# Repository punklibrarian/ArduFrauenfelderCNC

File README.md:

ArduFrauenfelderCNC
=============================
Copyright 2011 Design Tech Industries (DTI)  & Tamworth Hackerspace

DTI email: <the.righteous.avengers@gmail.com> |
THS: <http://tamworthhackerspace.org> |
Google Group: <https://groups.google.com/group/tamworth-hackerspace>

The ArduFrauenfelderCNC is a CNC mill run by an Arduino compatible custom board with 
stepper motor drivers, running grbl.

Board Features:

 * ATmega328 & ATmega32U4 MCU
 * Power LED & Reset switch
 * Populated pins for FTDI breakout board
 * SparkFun EasyDriver v4.4
 * Open Source; OSHW compliant
 * Design files freely available

Mill features:

 * Designed using free tools
 * Simple construction methods
 * Design files freely available

In this repository you will find the gerber files, project (.pro), board (.brd) and schematic (.sch), 
along with a grbl file configured specifically for the board.

**At the moment the files you find here are in the process of development and as such are not 
production ready. It is an ongoing endeavour to create the board and mill satisfactorily. If you can 
help in this regard please contact me, as well as if you find something that needs correction**

**The only files that can be manufactured are those of the ArduFrauenfelderCNC 1.0 - Arduino Pro Micro Edition. 
It should be a fully functional design. As on 20/07/2012 still untested.**

INSIDE THIS REPOSITORY
----------------------
The 'docs' folder within this repository includes a handy copy of the schematic in PNG format and images 
of the pcb/mill, along with assembly documentation.

The 'mill' folder within this repository has design files for the physical mill and documentation 
for it's construction. It has 'sketchup_exported_faces', 'sketchup_models' and 'laser_cutting' folders.
**For license information refer to the attached README.md file in the 'mill' folder**

The 'controller' folder within this repository has all the files needed to create the controller board. 
It has folders for the specific MCU used, 'ATmega328', 'ATmega32U4' (inside these folders are 'EAGLE', 'eagleUp', 
'KiCad' and 'gerbers' folders).

**For license information refer to the attached README.md file in the 'controller' folder**

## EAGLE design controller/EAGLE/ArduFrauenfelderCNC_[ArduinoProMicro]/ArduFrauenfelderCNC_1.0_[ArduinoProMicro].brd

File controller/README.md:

ArduFrauenfelderCNC >> Controller Board
=======================================
Copyright 2012 Design Tech Industries (DTI)  & Tamworth Hackerspace

In the 'controller' folder of this repository you can find the design files for the CNC controller board in an ATmega328 
and ATmega32U4 variety. You will find project files in EAGLE and KiCad formats, as well as completed gerber files for the 
board ready to be sent to BatchPCB and OSH Park, which are the the services I designed this board to use, for manufacture.

I have also added eagleUp (http://eagleup.wordpress.com) files as well as a SKP of the resulting conversion 
(minus parts as there aren't any at the moment).

You will also find a customised version of Grbl in the form of a .HEX file. Later versions of the controller 
board will use rStep and be based on the ATmega644p MCU (I am also looking at using an mbed and http://smoothieware.org).

INSTALLATION
------------
**EAGLE**
The design is saved as an EAGLE project. EAGLE PCB design software is available from www.cadsoftusa.com 
free for non-commercial use and can be installed on Windows and Mac, with Linux support through WINE. 
To use this project download it and place the directory containing these files into the "eagle" directory 
on your computer. Then open EAGLE and navigate to Projects -> eagle -> ArduFrauenfelderCNC.

**KiCad**
KiCad EDA Suite is an Open Source alternative to EAGLE. It is available on Windows and Linux and can be installed 
on Mac. It is available from http://kicad.sourceforge.net and works in a similar way to EAGLE. You will find project 
files for KiCad in the aptly named folder in this repository. To use this project download it and place the directory 
containing these files into a folder of your choice. Then open KiCad and navigate to File -> Open -> 
'FOLDER_OF_YOUR_CHOICE' -> ArduFrauenfelderCNC.pro

You will also find a manual in the 'docs' folder for the assembly of the controller board, with colour photos and diagrams. 
**Documentation is separately licensed. See LICENSE section below**

DISTRIBUTION
------------
The specific terms of distribution of this project are governed by the license referenced below.

LICENSE
-------
> CONTROLLER BOARD
> ----------------
> This work is licensed under the Creative Commons Attribution-ShareAlike License.  
> 
> To view a copy of this license, visit:
> 
>   http://creativecommons.org/licenses/by-sa/3.0/  
>   http://creativecommons.org/licenses/by-sa/3.0/legalcode
> 
> or send a letter to
> 
>   Creative Commons  
>   171 Second Street, Suite 300  
>   San Francisco  
>   California, 94105  
>   USA

> DOCUMENTATION
> -------------
> This work is licensed under the GNU Free Documentation License Version 1.3
> 
> To view a copy of this license, visit:
> 
>   http://www.gnu.org/licenses/fdl-1.3.html

The "license" folder within this repository also contains copies of the
license(s) referenced above.

CREDITS
-------
The ArduFrauenfelderCNC was designed by Jamie Johnston (jameskun89@rocketmail.com) 
based on previous work by the Arduino team (www.arduino.cc/playground/Main/People) 
which includes:

 * Massimo Banzi
 * David Cuartielles
 * Tom Igoe
 * Gianluca Martino
 * David A. Mellis

As well as Brian Schmalz, the creator of the EasyDriver Stepper Motor Driver (http://schmalzhaus.com/EasyDriver) 
and Sparkfun, the creator of the Arduino Pro Micro (http://www.sparkfun.com/products/11098).

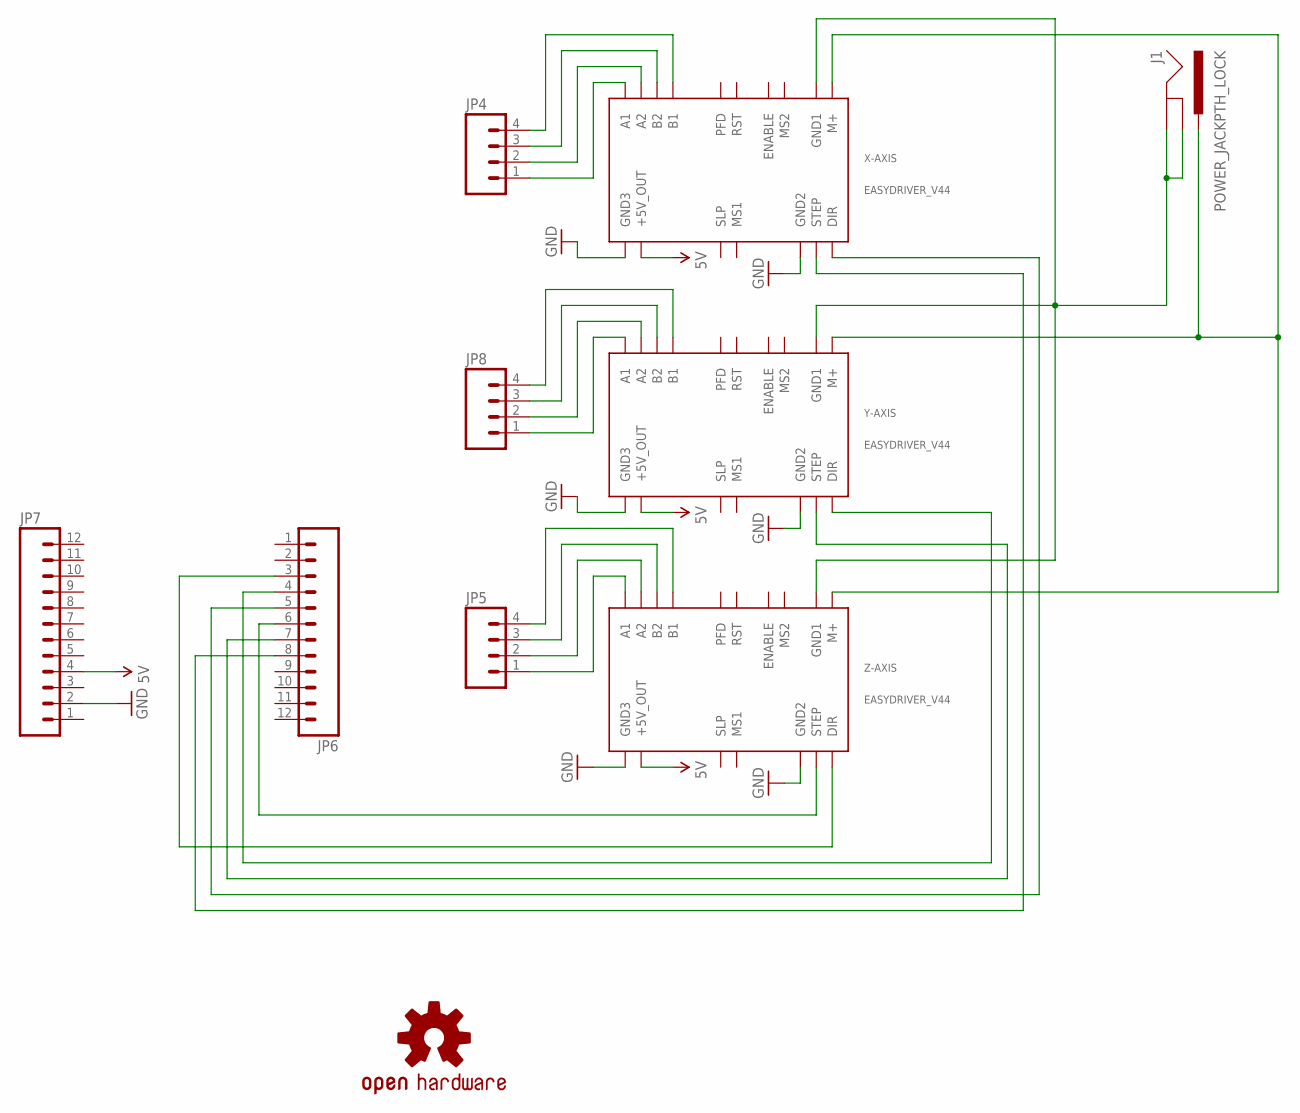
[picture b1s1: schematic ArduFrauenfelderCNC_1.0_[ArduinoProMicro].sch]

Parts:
J1: POWER_JACKPTH_LOCK; POWER_JACK_PTH_LOCK
JP4, JP5, JP8: M04LOCK_LONGPADS; 1X04_LOCK_LONGPADS
JP6, JP7: M12PTH; 1X12
U$2: OSHW-LOGOM; OSHW-LOGO-M
X-AXIS: EASYDRIVER_V44
Y-AXIS: EASYDRIVER_V44
Z-AXIS: EASYDRIVER_V44

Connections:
5V: JP7.4, X-AXIS.P$11 (+5V_OUT), Y-AXIS.P$11 (+5V_OUT), Z-AXIS.P$11 (+5V_OUT)
GND: JP7.2, X-AXIS.GND2, X-AXIS.GND3, Y-AXIS.GND2, Y-AXIS.GND3, Z-AXIS.GND2, Z-AXIS.GND3
unnamed: J1.GND, J1.GNDBREAK, X-AXIS.GND1, Y-AXIS.GND1, Z-AXIS.GND1
unnamed: JP4.1, X-AXIS.A1
unnamed: JP4.2, X-AXIS.A2
unnamed: J1.PWR, X-AXIS.M+, Y-AXIS.M+, Z-AXIS.M+
unnamed: JP4.3, X-AXIS.B2
unnamed: JP4.4, X-AXIS.B1
unnamed: JP8.1, Y-AXIS.A1
unnamed: JP8.2, Y-AXIS.A2
unnamed: JP8.3, Y-AXIS.B2
unnamed: JP8.4, Y-AXIS.B1
unnamed: JP5.1, Z-AXIS.A1
unnamed: JP5.2, Z-AXIS.A2
unnamed: JP5.3, Z-AXIS.B2
unnamed: JP5.4, Z-AXIS.B1
unnamed: JP6.8, X-AXIS.STEP
unnamed: JP6.5, X-AXIS.DIR
unnamed: JP6.7, Y-AXIS.STEP
unnamed: JP6.4, Y-AXIS.DIR
unnamed: JP6.6, Z-AXIS.STEP
unnamed: JP6.3, Z-AXIS.DIR

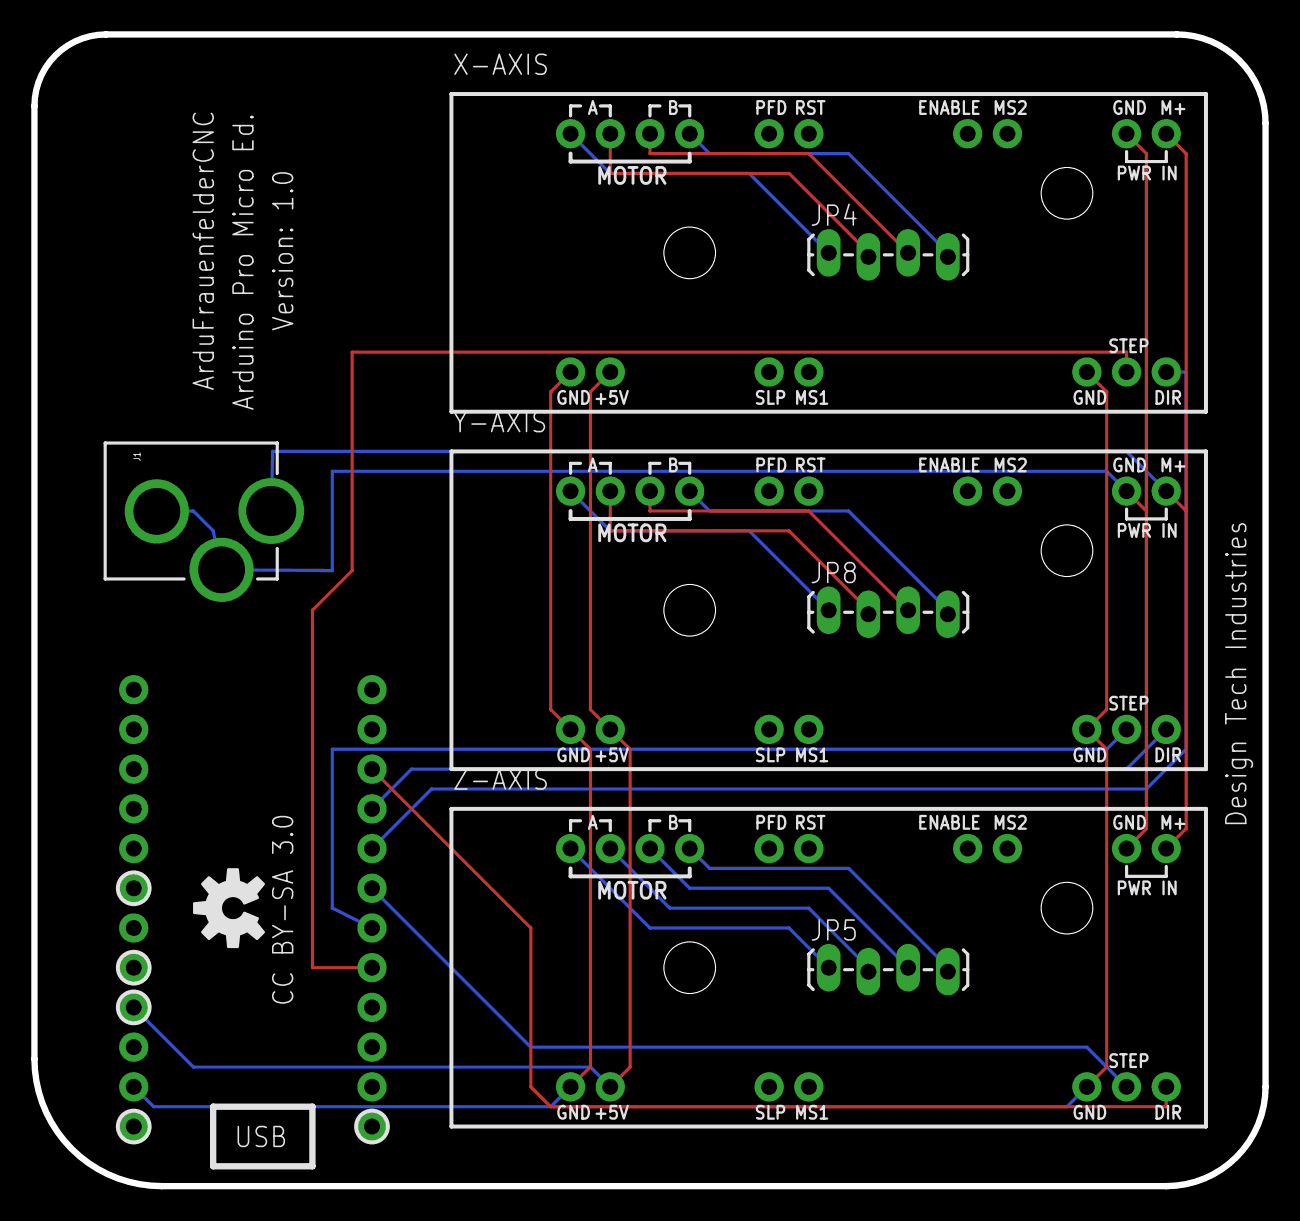
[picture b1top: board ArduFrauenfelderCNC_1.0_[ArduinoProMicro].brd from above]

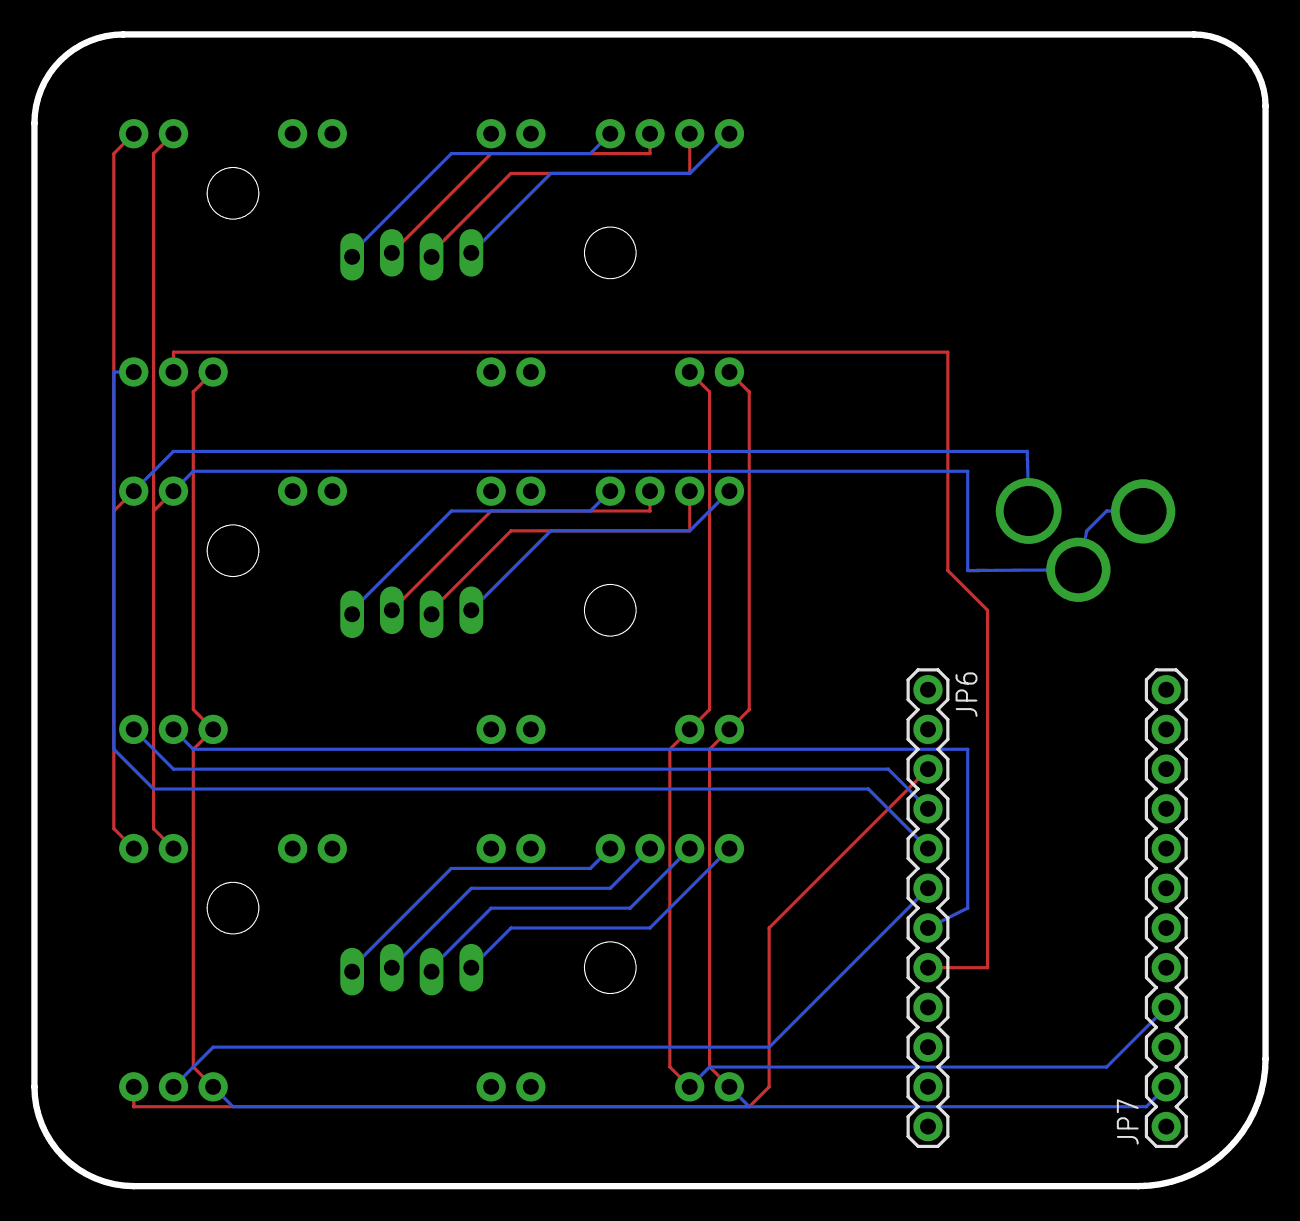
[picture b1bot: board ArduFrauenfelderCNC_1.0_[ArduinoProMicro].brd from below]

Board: 2 copper layers, 78.7 x 73.7 mm, 10 parts (2 on the bottom side), 22 nets.

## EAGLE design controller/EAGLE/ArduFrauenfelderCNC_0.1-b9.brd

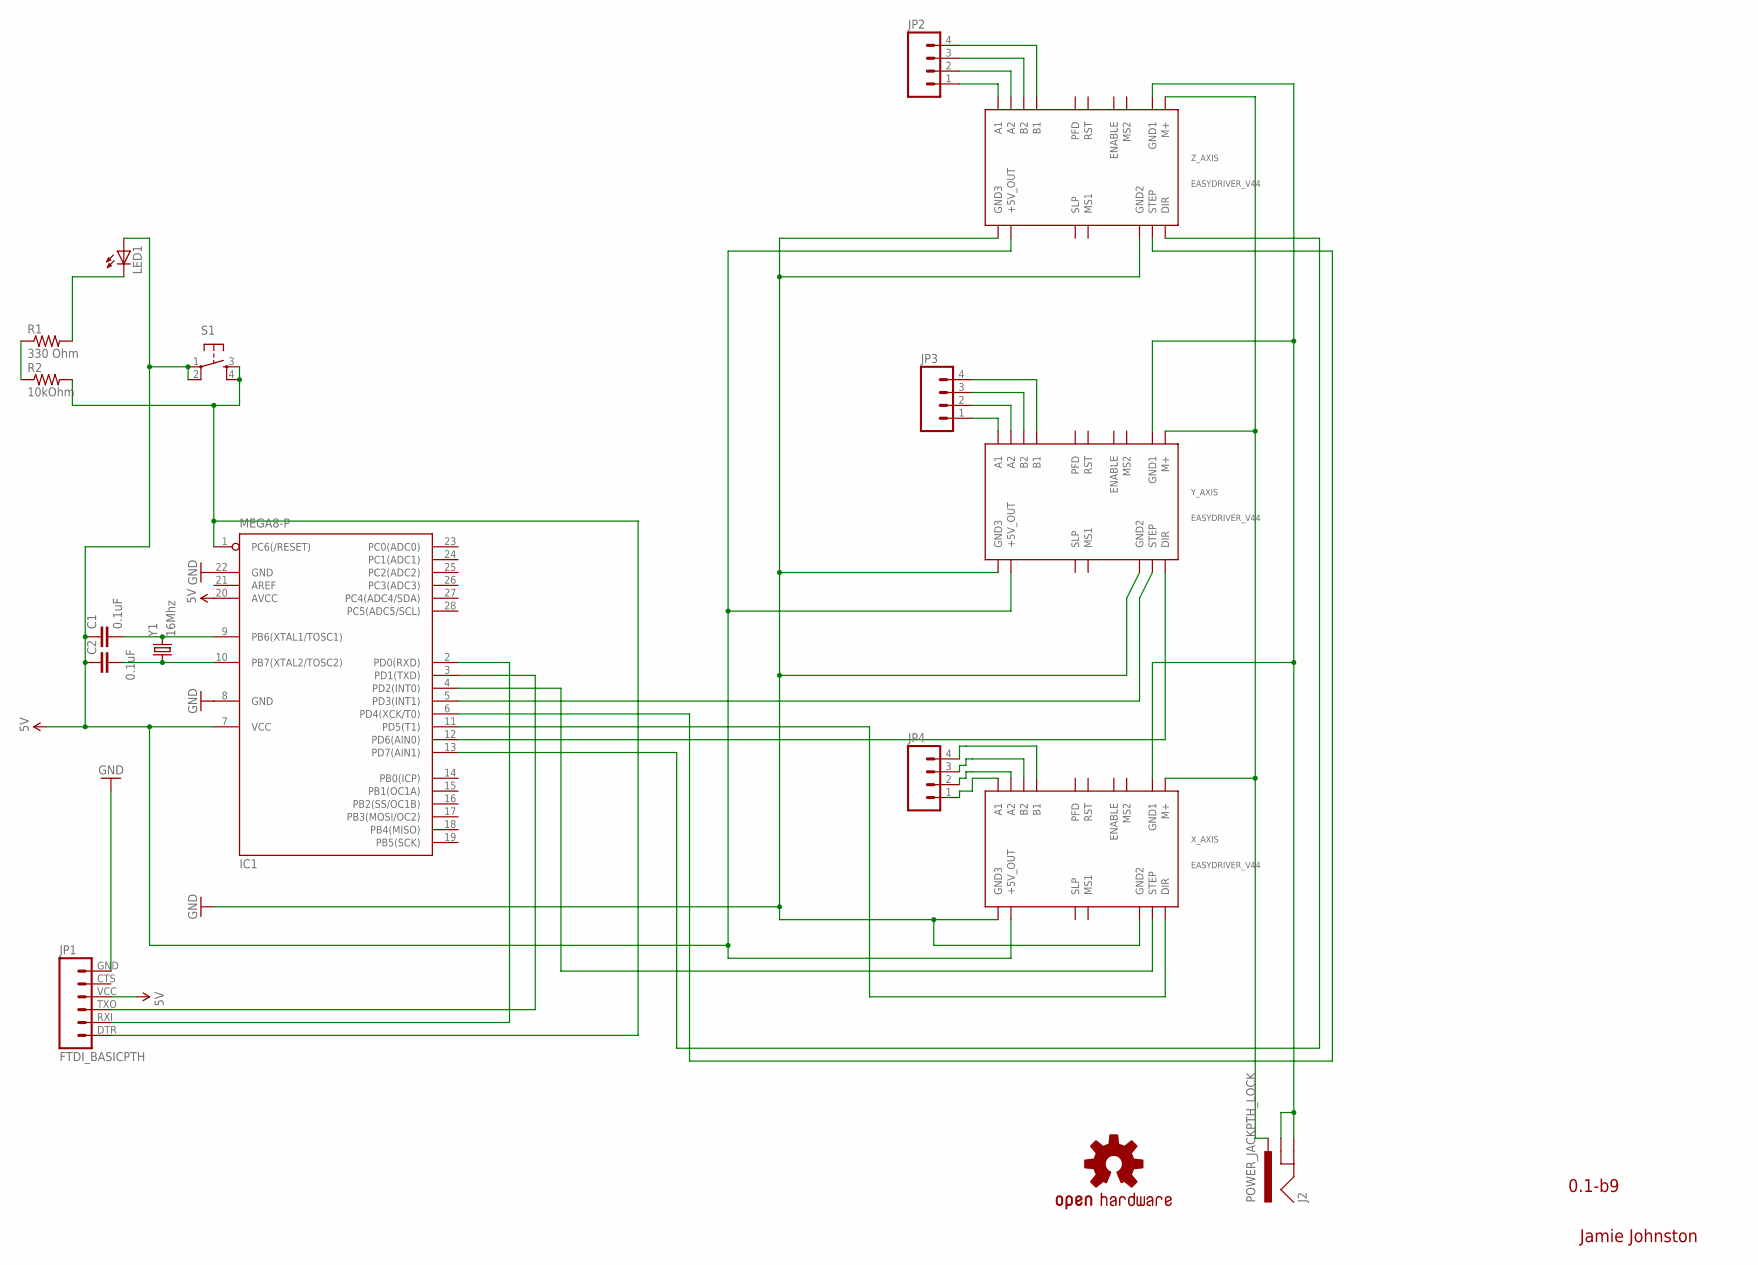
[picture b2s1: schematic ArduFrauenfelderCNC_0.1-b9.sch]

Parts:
C1, C2: 0.1uF; CAP-PTH-SMALL
IC1: MEGA8-P; DIL28-3
J2: POWER_JACKPTH_LOCK; POWER_JACK_PTH_LOCK
JP1: FTDI_BASICPTH; FTDI_BASIC
JP2, JP3, JP4: M04LOCK; 1X04_LOCK
LED1: LED5MM
R1: 330 Ohm; AXIAL-0.4
R2: 10kOhm; AXIAL-0.4
S1: TAC_SWITCHPTH; TACTILE-PTH
U$2: OSHW-LOGOL; OSHW-LOGO-L
X_AXIS: EASYDRIVER_V44
Y1: 16Mhz; HC49US
Y_AXIS: EASYDRIVER_V44
Z_AXIS: EASYDRIVER_V44

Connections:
5V: C1.1, C2.1, IC1.7 (VCC), IC1.20 (AVCC), JP1.VCC (4), LED1.A, S1.1, S1.2, X_AXIS.P$11 (+5V_OUT), Y_AXIS.P$11 (+5V_OUT), Z_AXIS.P$11 (+5V_OUT)
GND: IC1.8 (GND), IC1.22 (GND), JP1.GND (6), X_AXIS.GND2, X_AXIS.GND3, Y_AXIS.GND2, Y_AXIS.GND3, Z_AXIS.GND2, Z_AXIS.GND3
unnamed: C1.2, IC1.9 (PB6(XTAL1/TOSC1)), Y1.2
unnamed: C2.2, IC1.10 (PB7(XTAL2/TOSC2)), Y1.1
unnamed: IC1.5 (PD3(INT1)), Y_AXIS.STEP
unnamed: LED1.K (C), R1.P$2 (2)
unnamed: IC1.1 (PC6(/RESET)), JP1.DTR (1), R2.P$2 (2), S1.3, S1.4
unnamed: R1.P$1 (1), R2.P$1 (1)
unnamed: JP2.1, Z_AXIS.A1
unnamed: J2.PWR, X_AXIS.M+, Y_AXIS.M+, Z_AXIS.M+
unnamed: JP2.2, Z_AXIS.A2
unnamed: J2.GND, J2.GNDBREAK, X_AXIS.GND1, Y_AXIS.GND1, Z_AXIS.GND1
unnamed: IC1.3 (PD1(TXD)), JP1.TXO (3)
unnamed: IC1.2 (PD0(RXD)), JP1.RXI (2)
unnamed: IC1.12 (PD6(AIN0)), Y_AXIS.DIR
unnamed: IC1.4 (PD2(INT0)), X_AXIS.STEP
unnamed: JP2.3, Z_AXIS.B2
unnamed: IC1.11 (PD5(T1)), X_AXIS.DIR
unnamed: JP2.4, Z_AXIS.B1
unnamed: JP3.1, Y_AXIS.A1
unnamed: IC1.13 (PD7(AIN1)), Z_AXIS.DIR
unnamed: IC1.6 (PD4(XCK/T0)), Z_AXIS.STEP
unnamed: JP3.2, Y_AXIS.A2
unnamed: JP3.3, Y_AXIS.B2
unnamed: JP3.4, Y_AXIS.B1
unnamed: JP4.1, X_AXIS.A1
unnamed: JP4.2, X_AXIS.A2
unnamed: JP4.3, X_AXIS.B2
unnamed: JP4.4, X_AXIS.B1

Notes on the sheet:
Jamie Johnston
0.1-b9

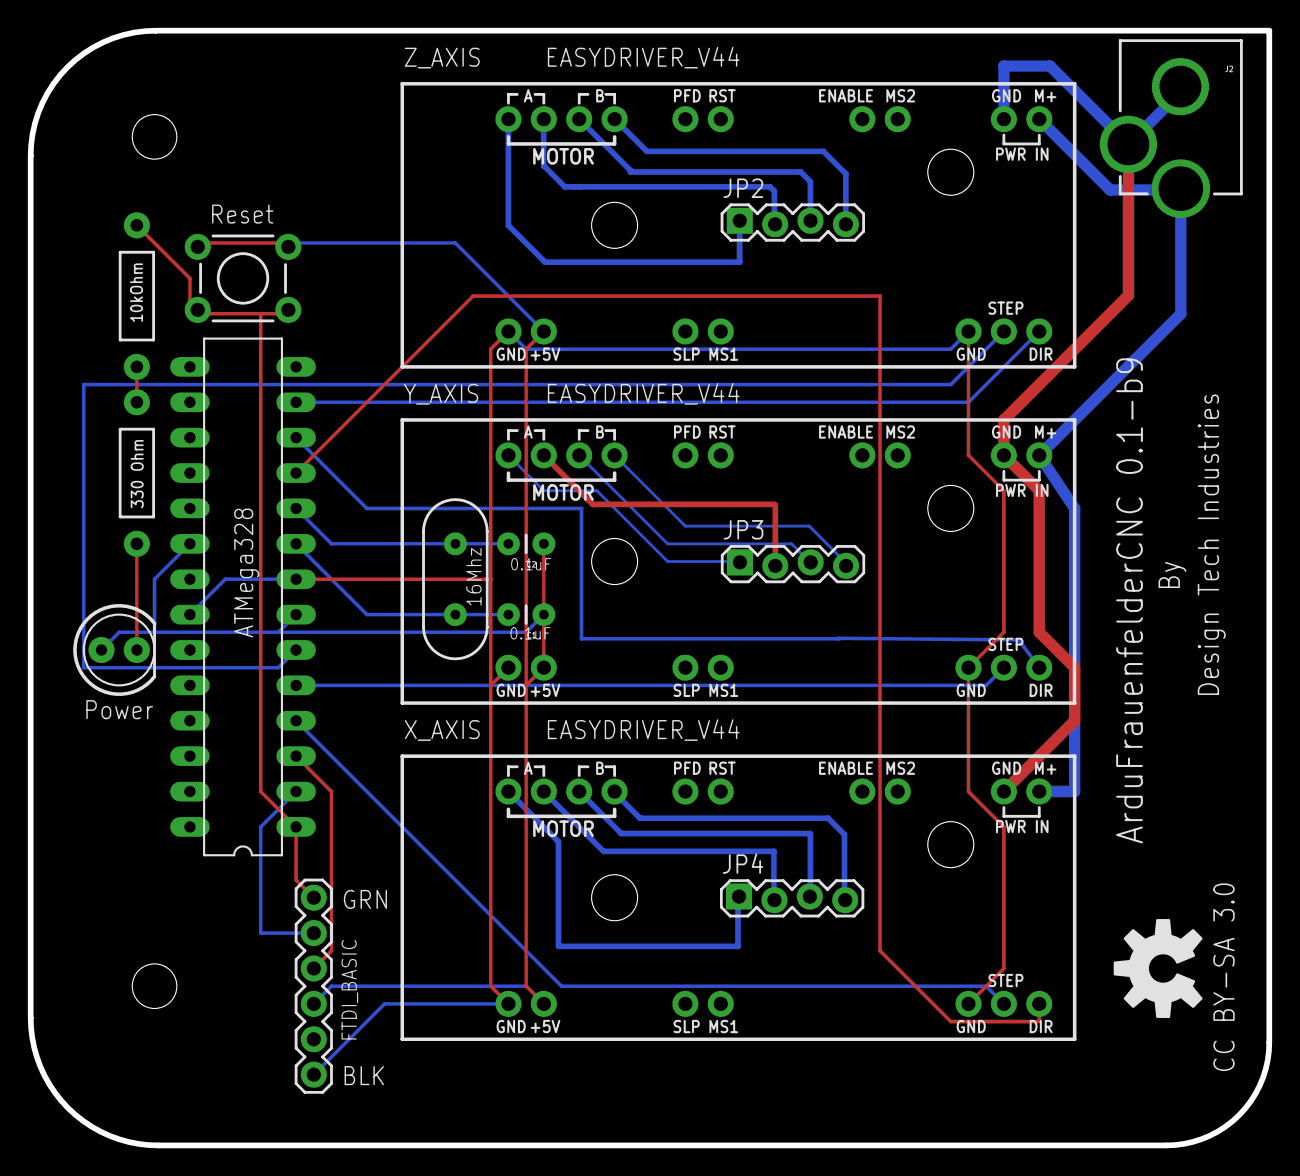
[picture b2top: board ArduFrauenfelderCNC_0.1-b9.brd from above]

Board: 2 copper layers, 88.9 x 80.0 mm, 17 parts (0 on the bottom side), 29 nets.

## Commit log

2011-11-18 Initial Commit -Jamie
2011-11-18 Edit to README.md formatting.
2011-11-18 Re-edit of README.md formatting.
2011-11-18 Changed file/folder structure so as to aid in program identification.
2011-11-19 Added Open Hardware symbol, board name, board version, board license (CC BY-SA 3.0), drill hole markers and reference to designing parties (DTI and THS).
2011-11-19 Found GND pins connected to +5v power pins. Rectified and traces are now more organised (only one jumper wire needed). Updated version to 0.1-b3.
2011-11-19 Conversion of EAGLE schematic to KiCad format (untested), using eagle2kicad.ulp V1.1
2011-11-19 Minor content change to README.md: added stop-gap material about included KiCad design files (more to be written later) and acknowledging Brian Schmalz in credits.
2011-11-19 New image of altered schematic (0.1-b2 => 0.1-b3), plus added version detail, OSHW logo and increase in image quality.
2011-11-19 Added version detail to schematic, as well as creators name and OSHW logo.
2011-11-19 Slight edit: added extra OSHW logo to board due to addition of logo to schematic.
2011-11-19 Update of schematic for KiCad (untested). Converted using eagle2kicad.ulp V1.1 and includes an initial commit of the .lib and .pro files.
2011-11-19 Minor edit: repositioned second OSHW logo, added GRN & BLK to tPlace layer and changed tDocu layer colour to yellow.
2011-11-20 Creation and initial commit of prototype Gerber files using SparkFun's CAM file (sfe-gerb274x.cam). Included are the seven files needed by fab houses and a tar.gz copy of files for ease of use.
2011-11-20 Altered README.md wording and added mention of Gerber files.
2011-11-20 Change to folder name.
2011-11-20 Changed README.md structure, adding what can found inside the repository and changed the description of project.
2011-11-20 Added license, GNU Free Documentation License Version Version 1.3, for future documentation. Also changed name of Creative Commons license to include version.
2011-11-20 Initial commit of 'mill' folder and its README.md file.
2011-11-20 Temporary delete.
2011-11-20 Re-commit of previously named 'Gerber' folder. Change of name to 'gerber'.
2011-11-20 Edit of content and formatting.
2011-11-20 Minor edit.
2011-11-20 Initial commit of board-specific grbl file.
2011-11-21 Incorrect Drill file found. Replaced with correct file and recompressed to tar.gz archive.
2011-11-22 Changed image naming scheme and added a board image.
2011-11-22 Moved PCB design related files to the 'controller' folder.
2011-11-22 Edited to reflect new folder structure.
2011-11-23 Initial commit of mill base and gantry in .SKP format.
2011-11-23 Added note about not using designs for production.
2011-11-24 Initial commit of Ponoko laser cutting templates in EPS and SVG formats [Please note that these have lots of wastage as they are my first attempts. Once design is complete wastage should be minimised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
2011-11-24 Initial commit of exported faces in SVG format from SketchUp of mill base and gantry.
2011-11-24 Added note about SVG and EPS files not ready for production and referenced addition to file structure.
2011-11-24 Added new gantry design to SKP file and new SVG export, as well as made models proper 3D versions. Deleted SVG and EPS templates.
2011-11-24 Moved SketchUp models to own folder and added separated models of the base and gantry.
2011-11-24 Changed end plate design of mill base to allow for Ponoko laser cutting, as well as changing the width of the gantry [I was made aware that it was too wide to fit into the base].
2011-11-24 Initial commit of SketchUp exported faces in SVG format.
2011-11-24 Removal of old files.
2011-11-24 Initial commit of Ponoko laser cutting templates. P3 sized boards with a small amount of wastage.
2011-11-25 Edited all README.md files and added one to the 'controller' folder.
2011-11-25 Change made to silkscreen layer to include component names and drill hole placement altered.
2011-11-25 Revert "Change made to silkscreen layer to include component names and drill hole placement altered."
    This reverts commit 92fa80944d13c01f441f73ab6e0e381a67eb5132.
2011-11-26 Minor edit to include 'eagleUp' folder in description.
2011-11-26 Removed due to new naming scheme.
2011-11-26 Removed due to new files being created.
2011-11-26 New gerber files generated.
2011-11-26 New eagle2kicad.ulp conversion.
2011-11-26 New board images, including an eagleUp image of bare board.
2011-11-26 New board version with errors corrected (0.1-b3 -> 0.1-b6). New naming scheme initiated.
2011-11-26 Initial commit of eagleUp files and SKP board file.
2011-11-26 New part included, Z-axis and drill platform [experimental]
2011-11-26 Added QR code to repository, license text and OSHW logo, and mills name to top side of milling surface.
2011-11-27 Removal due to name change.
2011-11-27 Change to trace placement and some connections.
2011-11-27 Removed due to new image.
2011-11-27 Updated for new board design. As well as having some components placed, including EasyDriver boards.
2011-11-27 Update due to new files being created.
2011-11-27 Updated SketchUp view of board.
2011-12-10 Commit of new board design files and DorkbotPDX gerber files.
2011-12-10 Commit of BatchPCB gerber compressed archive.
2011-12-13 Upgraded to EAGLE 6 and reserved files in new XML format.
2011-12-15 Updated design to 0.1-b9 [added three four-pin screw terminals for stepper motor connection].
2011-12-29 Upgrade to 0.1-b9 board design.
2012-01-27 Added experimental outlines to Laser Cutting templates [drill platform and Z axis]
2012-07-14 A general update of modified files [Includes new gantry and Z-axis design]
2012-07-14 First commit of consumable materials list.
2012-07-14 Added explanation to material_list.md
2012-07-14 Update to the gantry model to include linear bearing guides and manifold.
2012-07-14 Addition of controller board holder to main model SketchUp.
2012-07-14 Deletion of old/out-of-date files.
2012-07-14 Addition of 3D printed parts (Z-axis bearing housing), as well as 3D model and .dae of controller board holder. Included Ponoko laser cutting templates for reference.
2012-07-14 Changed naming scheme of .dae to play nice with Ponoko.
2012-07-15 Clean up of folder structure. Addition of Z-axis linear bearing manifold
2012-07-15 Updated gantry design. Changed name of all-in-one model file.
2012-07-15 Changed email address in README.md file.
2012-07-19 Restructure of folders. Initial commit of additional board design. Update to KiCAD files. Renamed 'DorkbotPDX' to the new 'OSH Park'.
    I have moved files from a general folder structure to a board specific
    structure, i.e: 'ArduFrauenfelderCNC' and
    'ArduFrauenfelderCNC_[ArduinoProMicro]'.
    The new controller board uses an Arduino Pro Micro, taking away the
    need for a FTDI adaptor and smartening things up. I will of course
    continue developing the cheaper on-board Arduino version but this is a
2012-07-19 Change made to complete model .skp file to include new controller board holder, as well as schematic & board images.
2012-07-20 Changed folder structure to be MCU specific, moving designs into 'ATmega328' and 'ATmega32U4' folders. Updated REAME.md's to reflect changes.
2012-07-20 General folder house keeping.
